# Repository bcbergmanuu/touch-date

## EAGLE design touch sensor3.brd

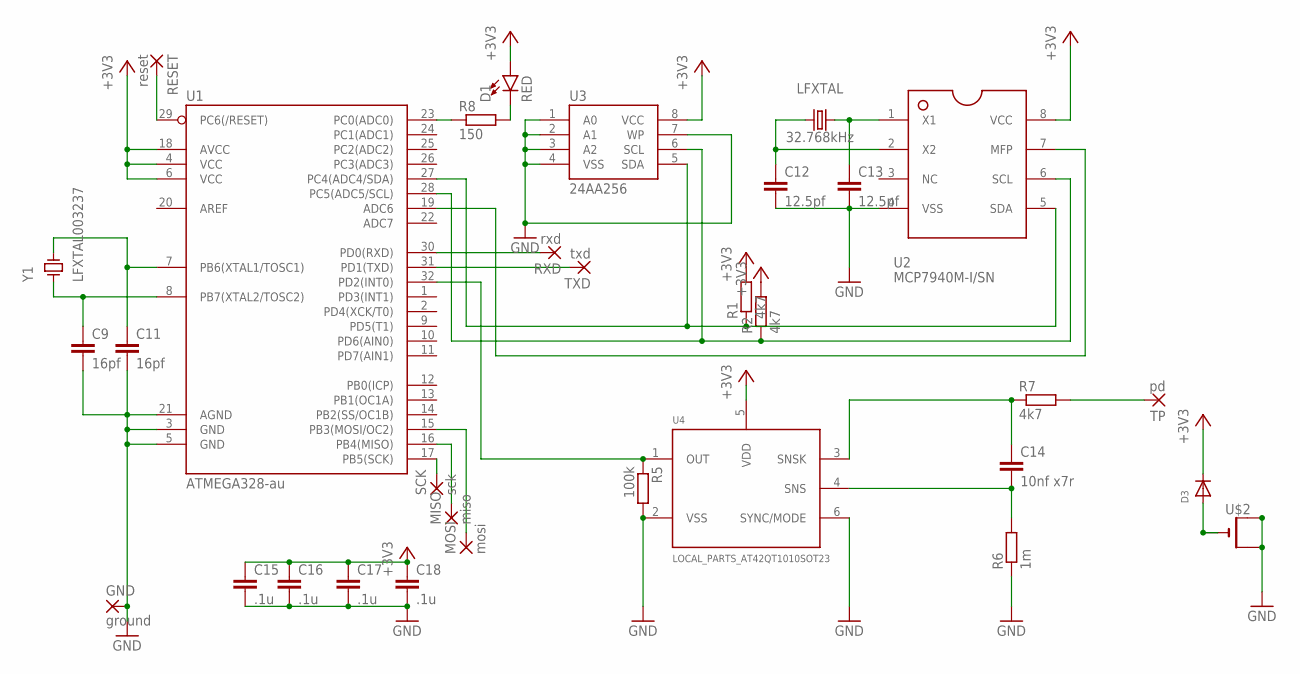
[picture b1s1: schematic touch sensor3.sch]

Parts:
C9, C11: 16pf; C0805
C12, C13: 12.5pf; C0805
C14: 10nf x7r; C0805
C15, C16, C17, C18: .1u; C0805
D1: RED; LED-0603
D3: DIODESMA; SMADIODE
GND: ground; SMD1,27-2,54
LFXTAL: 32.768kHz; CRYSTAL-PTH-2X6-CYL
MISO: miso; SMD1,27-2,54
MOSI: mosi; SMD1,27-2,54
R1, R2: 4k7; M0805
R5: 100k; R0805
R6: 1m; R0805
R7: 4k7; R0805
R8: 150; R0805
RESET: reset; SMD1,27-2,54
RXD: rxd; SMD1,27-2,54
SCK: sck; SMD1,27-2,54
TP: pd; SMD1,27-2,54
TXD: txd; SMD1,27-2,54
U1: ATMEGA328-au; TQFP32-08
U2: MCP7940M-I/SN; SO08
U3: 24AA256; SO08
U4: LOCAL_PARTS_AT42QT1010SOT23; LOCAL_PARTS_SOT23-6
U$2: CR2032SMT; CR2032-SMD
Y1: LFXTAL003237; XTAL1140X490X430N

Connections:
+3V3: C15.1, C16.1, C17.1, C18.1, D1.A, D3.C, R1.2, R2.2, U1.4 (VCC), U1.6 (VCC), U1.18 (AVCC), U2.8 (VCC), U3.8 (VCC), U4.5 (VDD)
GND: C9.2, C11.2, C12.2, C13.2, C15.2, C16.2, C17.2, C18.2, GND.1, R5.2, R6.1, U1.3 (GND), U1.5 (GND), U1.21 (AGND), U2.4 (VSS), U3.1 (A0), U3.2 (A1), U3.3 (A2), U3.4 (VSS), U3.7 (WP), U4.2 (VSS), U4.6 (SYNC/MODE), U$2.+$1 (+), U$2.+$2 (+1)
unnamed: C13.1, LFXTAL.2, U2.1 (X1)
unnamed: C12.1, LFXTAL.1, U2.2 (X2)
unnamed: R1.1, U1.27 (PC4(ADC4/SDA)), U2.5 (SDA), U3.5 (SDA)
unnamed: R2.1, U1.28 (PC5(ADC5/SCL)), U2.6 (SCL), U3.6 (SCL)
unnamed: C11.1, U1.7 (PB6(XTAL1/TOSC1)), Y1.2
unnamed: R5.1, U1.32 (PD2(INT0)), U4.1 (OUT)
unnamed: C9.1, U1.8 (PB7(XTAL2/TOSC2)), Y1.1
unnamed: R8.1, U1.23 (PC0(ADC0))
unnamed: D1.C, R8.2
unnamed: C14.2, R6.2, U4.4 (SNS)
unnamed: C14.1, R7.1, U4.3 (SNSK)
unnamed: R7.2, TP.1
unnamed: RESET.1, U1.29 (PC6(/RESET))
unnamed: U1.19 (ADC6), U2.7 (MFP)
unnamed: RXD.1, U1.30 (PD0(RXD))
unnamed: TXD.1, U1.31 (PD1(TXD))
unnamed: SCK.1, U1.17 (PB5(SCK))
unnamed: MISO.1, U1.16 (PB4(MISO))
unnamed: MOSI.1, U1.15 (PB3(MOSI/OC2))
VBAT: D3.A, U$2.-

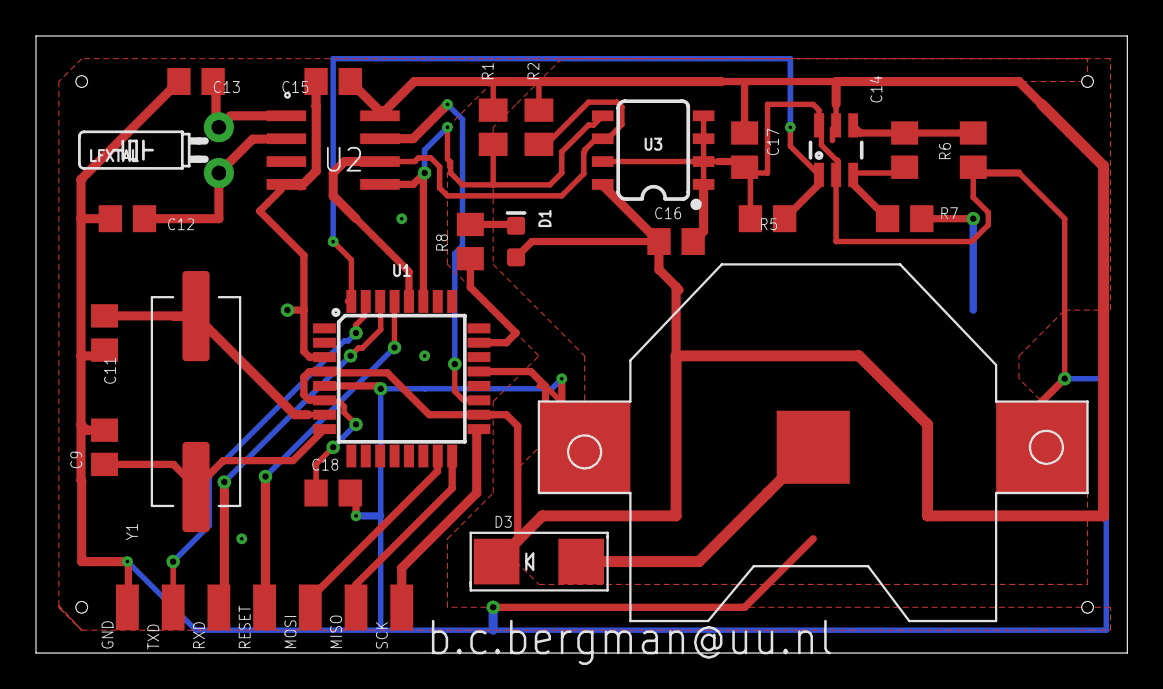
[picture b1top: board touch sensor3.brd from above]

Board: 2 copper layers, 60.6 x 34.3 mm, 32 parts (1 on the bottom side), 22 nets.

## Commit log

2020-08-04 working
2020-08-15 Version 1.0 Changed to workable version
2020-08-16 rename

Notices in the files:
parts and their libraries:
SparkFun-LED: Licensing: Creative Commons ShareAlike 4.0 International - https://creativecommons.org/licenses/by-sa/4.0
